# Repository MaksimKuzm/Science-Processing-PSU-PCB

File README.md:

# Science-Processing-PSU-PCB
PCB for the power supply of the science processing.

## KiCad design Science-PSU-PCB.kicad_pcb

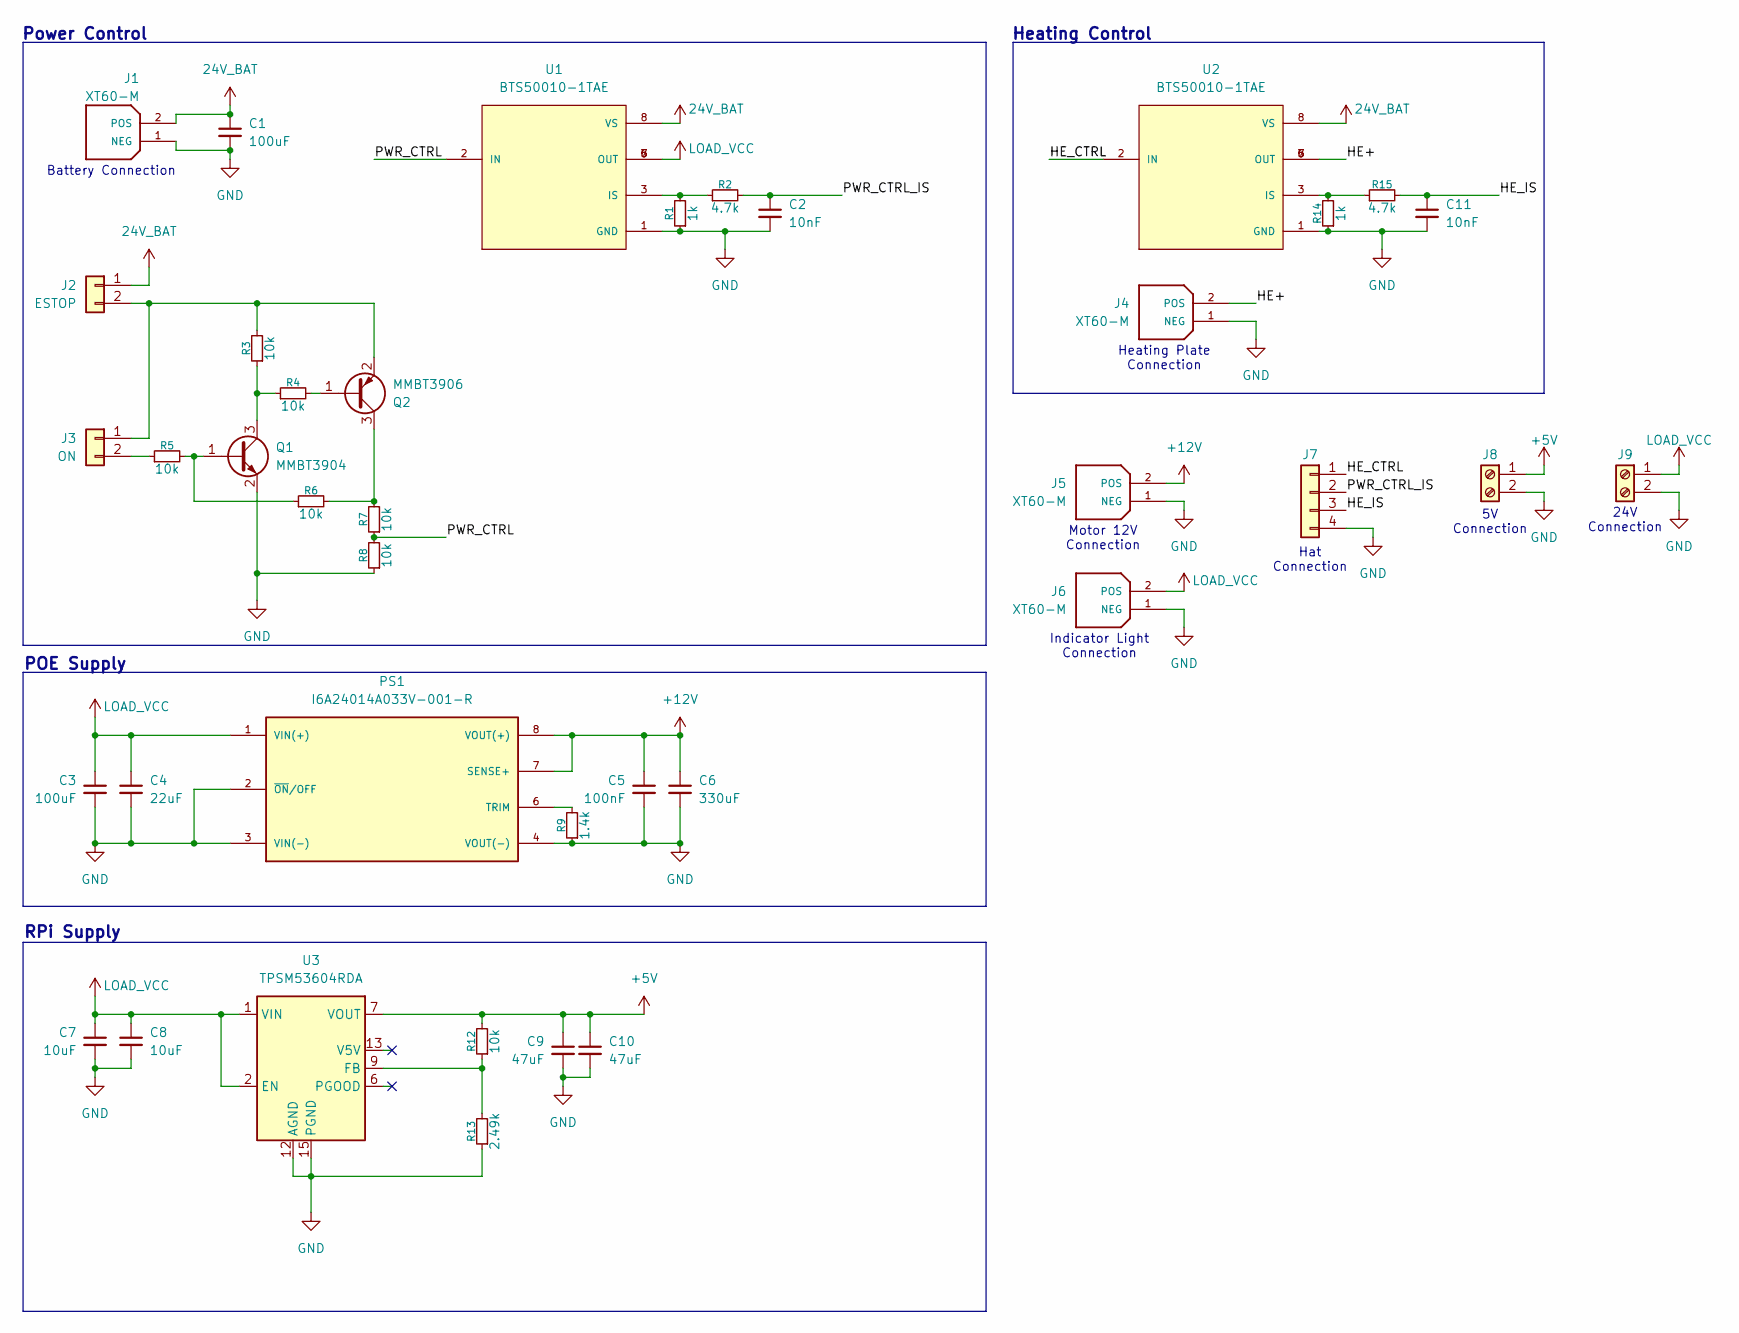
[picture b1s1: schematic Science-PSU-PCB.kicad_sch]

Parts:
C1, C3: 100uF; CP_Elec_8x10
C2, C11: 10nF; C_0805_2012Metric_Pad1.18x1.45mm_HandSolder
C4: 22uF; C_Radial_D5.0mm_H11.0mm_P2.00mm
C5: 100nF; C_0805_2012Metric_Pad1.18x1.45mm_HandSolder
C6: 330uF; C_Radial_D10.0mm_H12.5mm_P5.00mm
C7, C8: 10uF; C_1206_3216Metric_Pad1.33x1.80mm_HandSolder
C9, C10: 47uF; C_1206_3216Metric_Pad1.33x1.80mm_HandSolder
J1, J4, J5, J6: XT60-M; AMASS_XT60IPW-M_1x03_P7.20mm_Horizontal; PARTREV V1.2
J2: ESTOP; JST_XH_S2B-XH-A-1_1x02_P2.50mm_Horizontal
J3: ON; JST_XH_S2B-XH-A-1_1x02_P2.50mm_Horizontal
J7: Conn_01x04; JST_XH_S4B-XH-A-1_1x04_P2.50mm_Horizontal
J8, J9: Screw_Terminal_01x02; TerminalBlock_bornier-2_P5.08mm
PS1: I6A24014A033V-001-R; PARTREV A2
Q1: MMBT3904; SOT-23
Q2: MMBT3906; SOT-23
R1, R14: 1k; R_0805_2012Metric_Pad1.20x1.40mm_HandSolder
R2, R15: 4.7k; R_0805_2012Metric_Pad1.20x1.40mm_HandSolder
R3, R4, R5, R6, R7, R8, R12: 10k; R_0805_2012Metric_Pad1.20x1.40mm_HandSolder
R9: 1.4k; R_0805_2012Metric_Pad1.20x1.40mm_HandSolder
R13: 2.49k; R_0805_2012Metric_Pad1.20x1.40mm_HandSolder
U1, U2: BTS50010-1TAE; PARTREV 1.0
U3: TPSM53604RDA; Texas_B3QFN-14-1EP_5x5.5mm_P0.65mm_ThermalVia

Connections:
24V_BAT: C1.1, J1.2 (POS), J2.1, U1.8 (VS), U2.8 (VS)
+5V: C9.1, C10.1, J8.1, R12.2, U3.7 (VOUT), U3.8 (VOUT)
+12V: C5.1, C6.1, J5.2 (POS), PS1.7 (SENSE+), PS1.8 (VOUT(+))
/HE+: J4.2 (POS), U2.5 (OUT), U2.6 (OUT), U2.7 (OUT)
/HE_CTRL: J7.1, U2.2 (IN)
/HE_IS: C11.1, J7.3, R15.2
/PWR_CTRL: R7.1, R8.2, U1.2 (IN)
/PWR_CTRL_IS: C2.1, J7.2, R2.2
GND: C1.2, C2.2, C3.2, C4.2, C5.2, C6.2, C7.2, C8.2, C9.2, C10.2, C11.2, J1.1 (NEG), J4.1 (NEG), J5.1 (NEG), J6.1 (NEG), J7.4, J8.2, J9.2, PS1.2 (~ON/OFF), PS1.3 (VIN(-)), PS1.4 (VOUT(-)), Q1.2 (E), R1.1, R8.1, R9.1, R13.1, R14.1, U1.1 (GND), U2.1 (GND), U3.3 (PGND), U3.10 (PGND), U3.11 (PGND), U3.12 (AGND), U3.15 (PGND)
LOAD_VCC: C3.1, C4.1, C7.1, C8.1, J6.2 (POS), J9.1, PS1.1 (VIN(+)), U1.5 (OUT), U1.6 (OUT), U1.7 (OUT), U3.1 (VIN), U3.2 (EN), U3.14 (VIN)
unnamed: J2.2, J3.1, Q2.2 (E), R3.2
unnamed: J3.2, R5.1
unnamed: PS1.6 (TRIM), R9.2
unnamed: Q1.1 (B), R5.2, R6.1
unnamed: Q1.3 (C), R3.1, R4.1
unnamed: Q2.1 (B), R4.2
unnamed: Q2.3 (C), R6.2, R7.2
unnamed: R1.2, R2.1, U1.3 (IS)
unnamed: R14.2, R15.1, U2.3 (IS)
unnamed: R12.1, R13.2, U3.9 (FB)

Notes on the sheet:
Hat Connection
Heating Control
POE Supply
5V Connection
Indicator Light Connection
Heating Plate Connection
RPi Supply
Power Control
Motor 12V Connection
24V Connection
Battery Connection

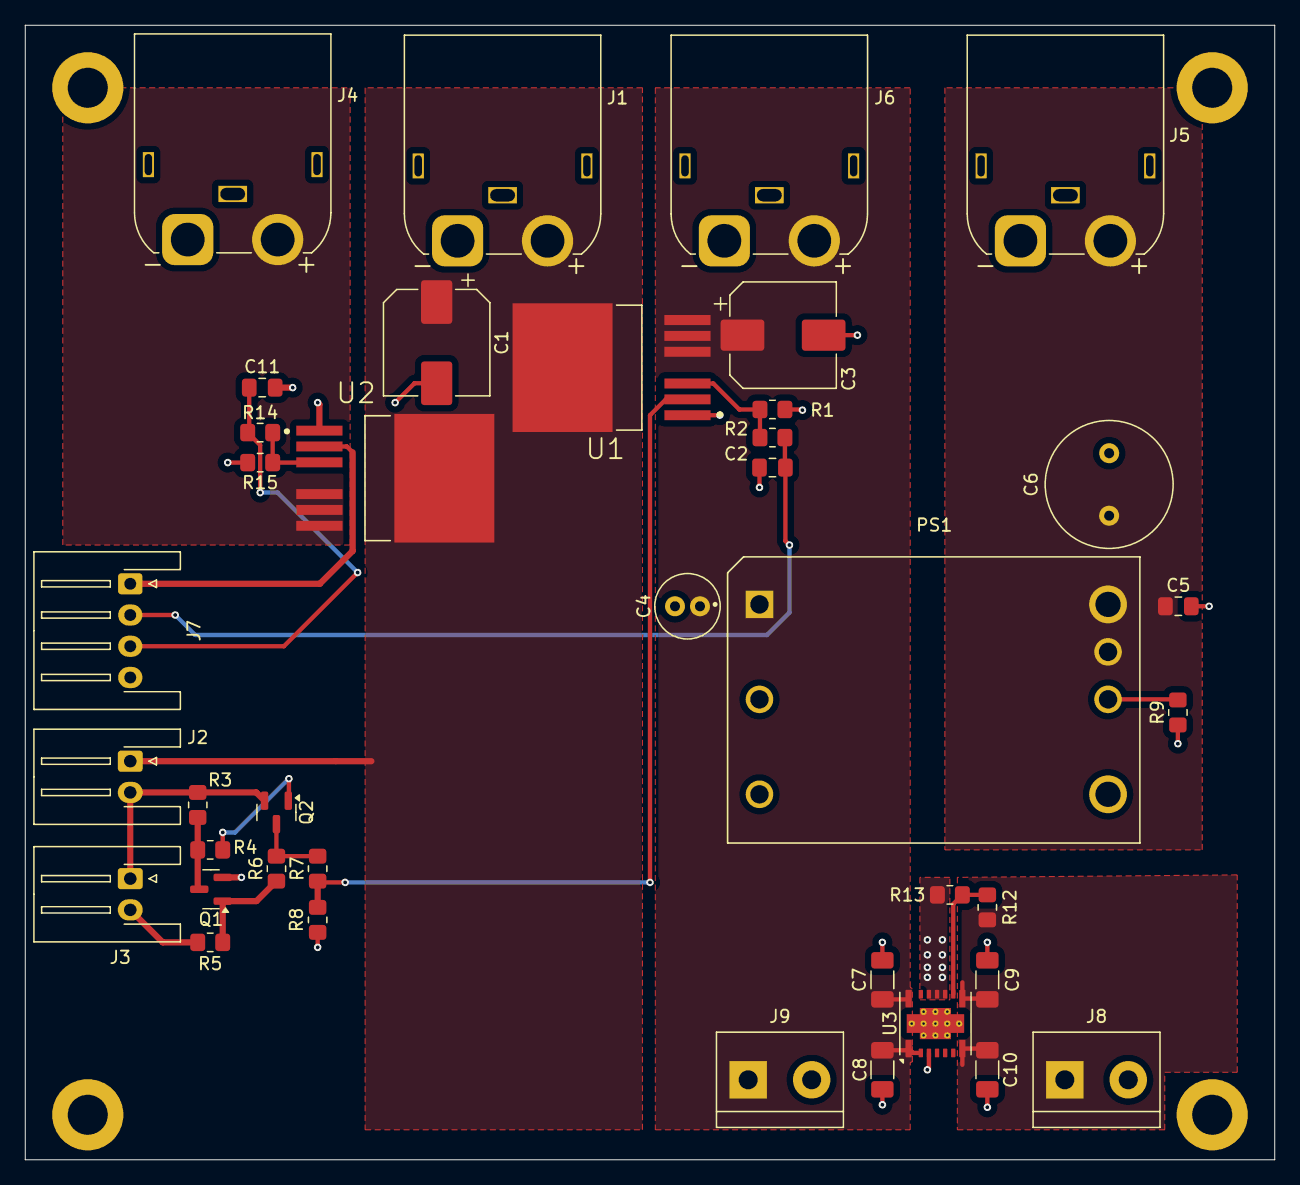
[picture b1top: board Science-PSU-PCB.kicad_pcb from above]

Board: 2 copper layers, 100.0 x 90.8 mm, 39 parts (0 on the bottom side), 20 nets.

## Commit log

2025-10-02 Test
2025-10-02 Started schematic
2025-10-02 PCB Layout and routing.
2025-10-06 Changed vertical to horizontal connectors
